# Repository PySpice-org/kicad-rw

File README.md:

# KiCad-RW : Python library to read/write KiCad Sexpr file format

[![KiCadRW
license](https://img.shields.io/pypi/l/KiCadRW.svg)](https://pypi.python.org/pypi/KiCadRW)
[![KiCadRW python
version](https://img.shields.io/pypi/pyversions/KiCadRW.svg)](https://pypi.python.org/pypi/KiCadRW)

[![KiCadRW last
version](https://img.shields.io/pypi/v/KiCadRW.svg)](https://pypi.python.org/pypi/KiCadRW)

**Quick Links**

  - [Devel Branch](https://github.com/FabriceSalvaire/kicad-rw/tree/devel)
  - [Production Branch](https://github.com/FabriceSalvaire/kicad-rw/tree/master)

## Overview

### What is KiCaD-RW ?

**A WORK IN PROGRESS...**

**keywords:** kicad, 6, sexpr, python, schema

**KiCad-RW** is a Python module to read the KiCad version 6 schema file format
(<span class="title-ref">.kicad\_sch</span> file extension) and to compute the netlist which is not
actually stored by KiCad. This module is standalone and independent of the KiCad Python API, thus it
don't require KiCad to work.

**Examples of use cases:**

  - perform checks on circuit
  - export a BOM
  - generate a customised SPICE netlist, see [PySpice](https://github.com/FabriceSalvaire/PySpice)
  - generate a [LaTeX/Tikz](https://ctan.org/pkg/pgf?lang=en) graphic **TO BE IMPLEMENTED**
  - generate a draft for [Circuit\_macros](https://ece.uwaterloo.ca/~aplevich/Circuit_macros), a
    tool for drawing electric high quality circuits, see
    <span class="title-ref">CircuitMacrosDumper</span>
  - etc.

**KiCad-RW** uses the Python library [sexpdata](https://github.com/jd-boyd/sexpdata) to parse the
file.

**How to go further:**

  - KiCad uses Sexpr format, thus we don't have so many tools and a DTD like for XML
  - We must use an external library to parse Sexpr format: sexpdata actually
  - We must be able to parse the file without the need of KiCad, especially if we think KiCad is a
    reference EDA software
  - We must not write tons of code to handle this format...
  - We must try to auto-learn the KiCad format from a reference file collection and generate an OO
    API (fully automatic, jinja template)

[Look at this project](https://github.com/FabriceSalvaire/kicad-rw/projects/1)

[Comprehensive bibliography and relevant links on the
topic](https://github.com/FabriceSalvaire/kicad-rw/blob/main/LINKS.md)

### Where is the Documentation ?

*TO BE COMPLETED*

### Where to get help or talk about KiCaD-RW ?

*TO BE COMPLETED*:

### What are the main features ?

### How to install it ?

*TO BE COMPLETED*

## Pull Request Recommendation

To make it easier to merge your pull request, you should divide your PR into smaller and
easier-to-verify units.

Please do not make a pull requests with a lot of modifications which are difficult to check.

## Credits

Authors: [Fabrice Salvaire](http://fabrice-salvaire.fr) and
[contributors](https://github.com/FabriceSalvaire/kicad-rw/blob/master/CONTRIBUTORS.md)

## News

### V0 2020-05-xx

Started project...

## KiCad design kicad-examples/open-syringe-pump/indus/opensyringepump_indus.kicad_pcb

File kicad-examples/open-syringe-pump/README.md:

# OpenSyringePump Project

Example of a four-layer CMS board designed with KiCad by the [Electrolab](https://www.electrolab.fr)
team (Mehdi Khairy) during the Covid-19 pandemy to make an open hardware syringe pump, the
[OpenSyringePump](https://www.opensyringepump.com/en/design-bom/electronic-parts) project.

All documents are hosted on this Git repository
https://code.electrolab.fr/covid-19/opensyringepump/-/tree/master/hardware/indus/opensyringe_indus

## Hardware License

The **OpenSyringePump** project led by the **ELECTROLAB** non profit organization, and all documents
produced through the development process are under Creative Commons license:
https://creativecommons.org/licenses/by-sa/4.0

See for more details https://www.opensyringepump.com/en/project-license

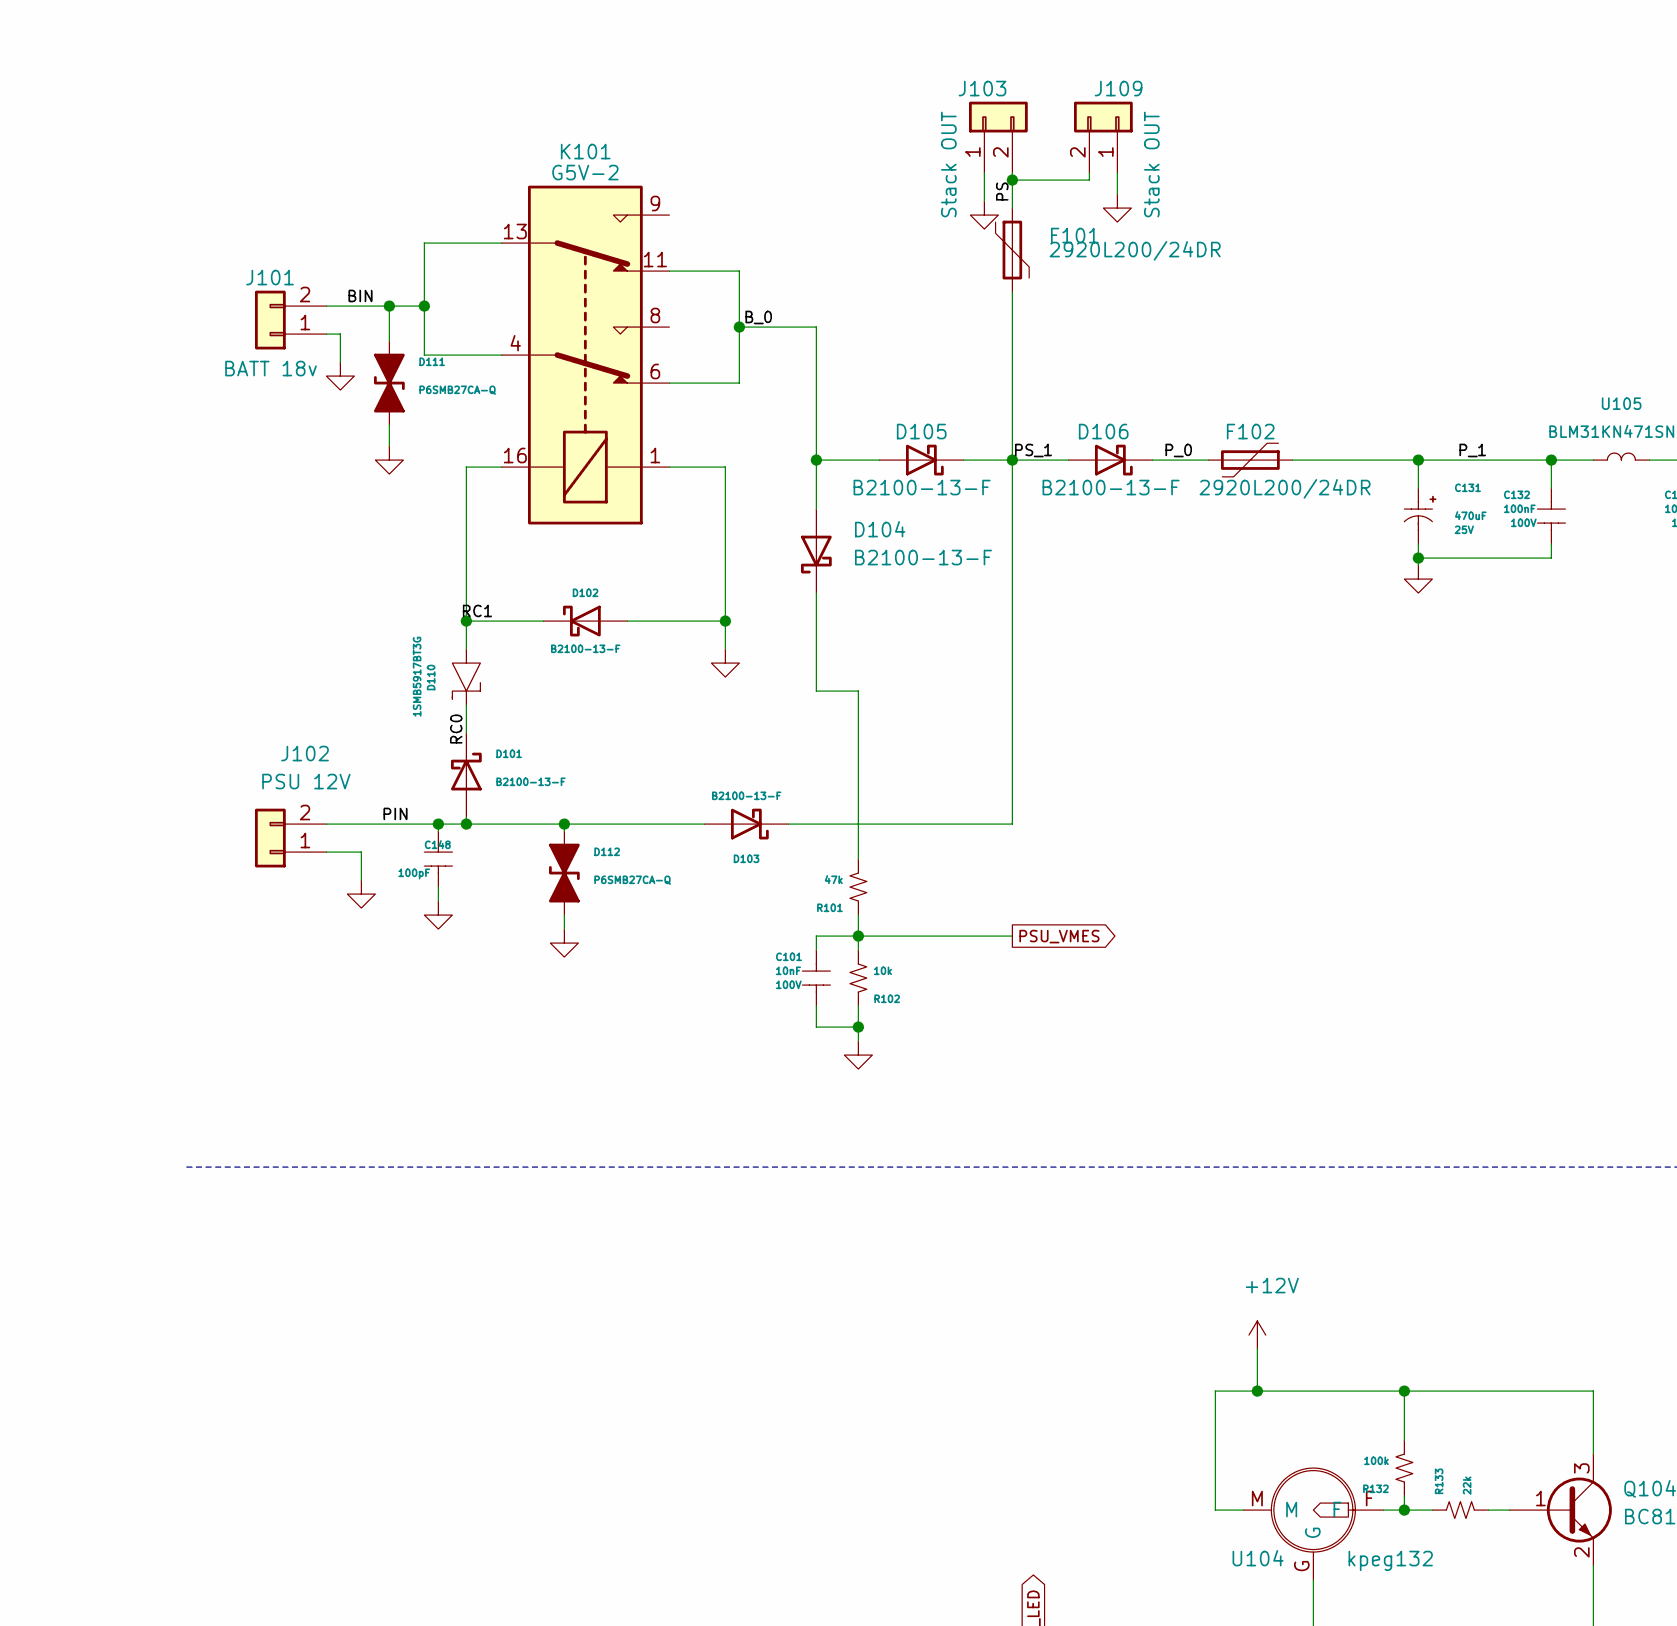
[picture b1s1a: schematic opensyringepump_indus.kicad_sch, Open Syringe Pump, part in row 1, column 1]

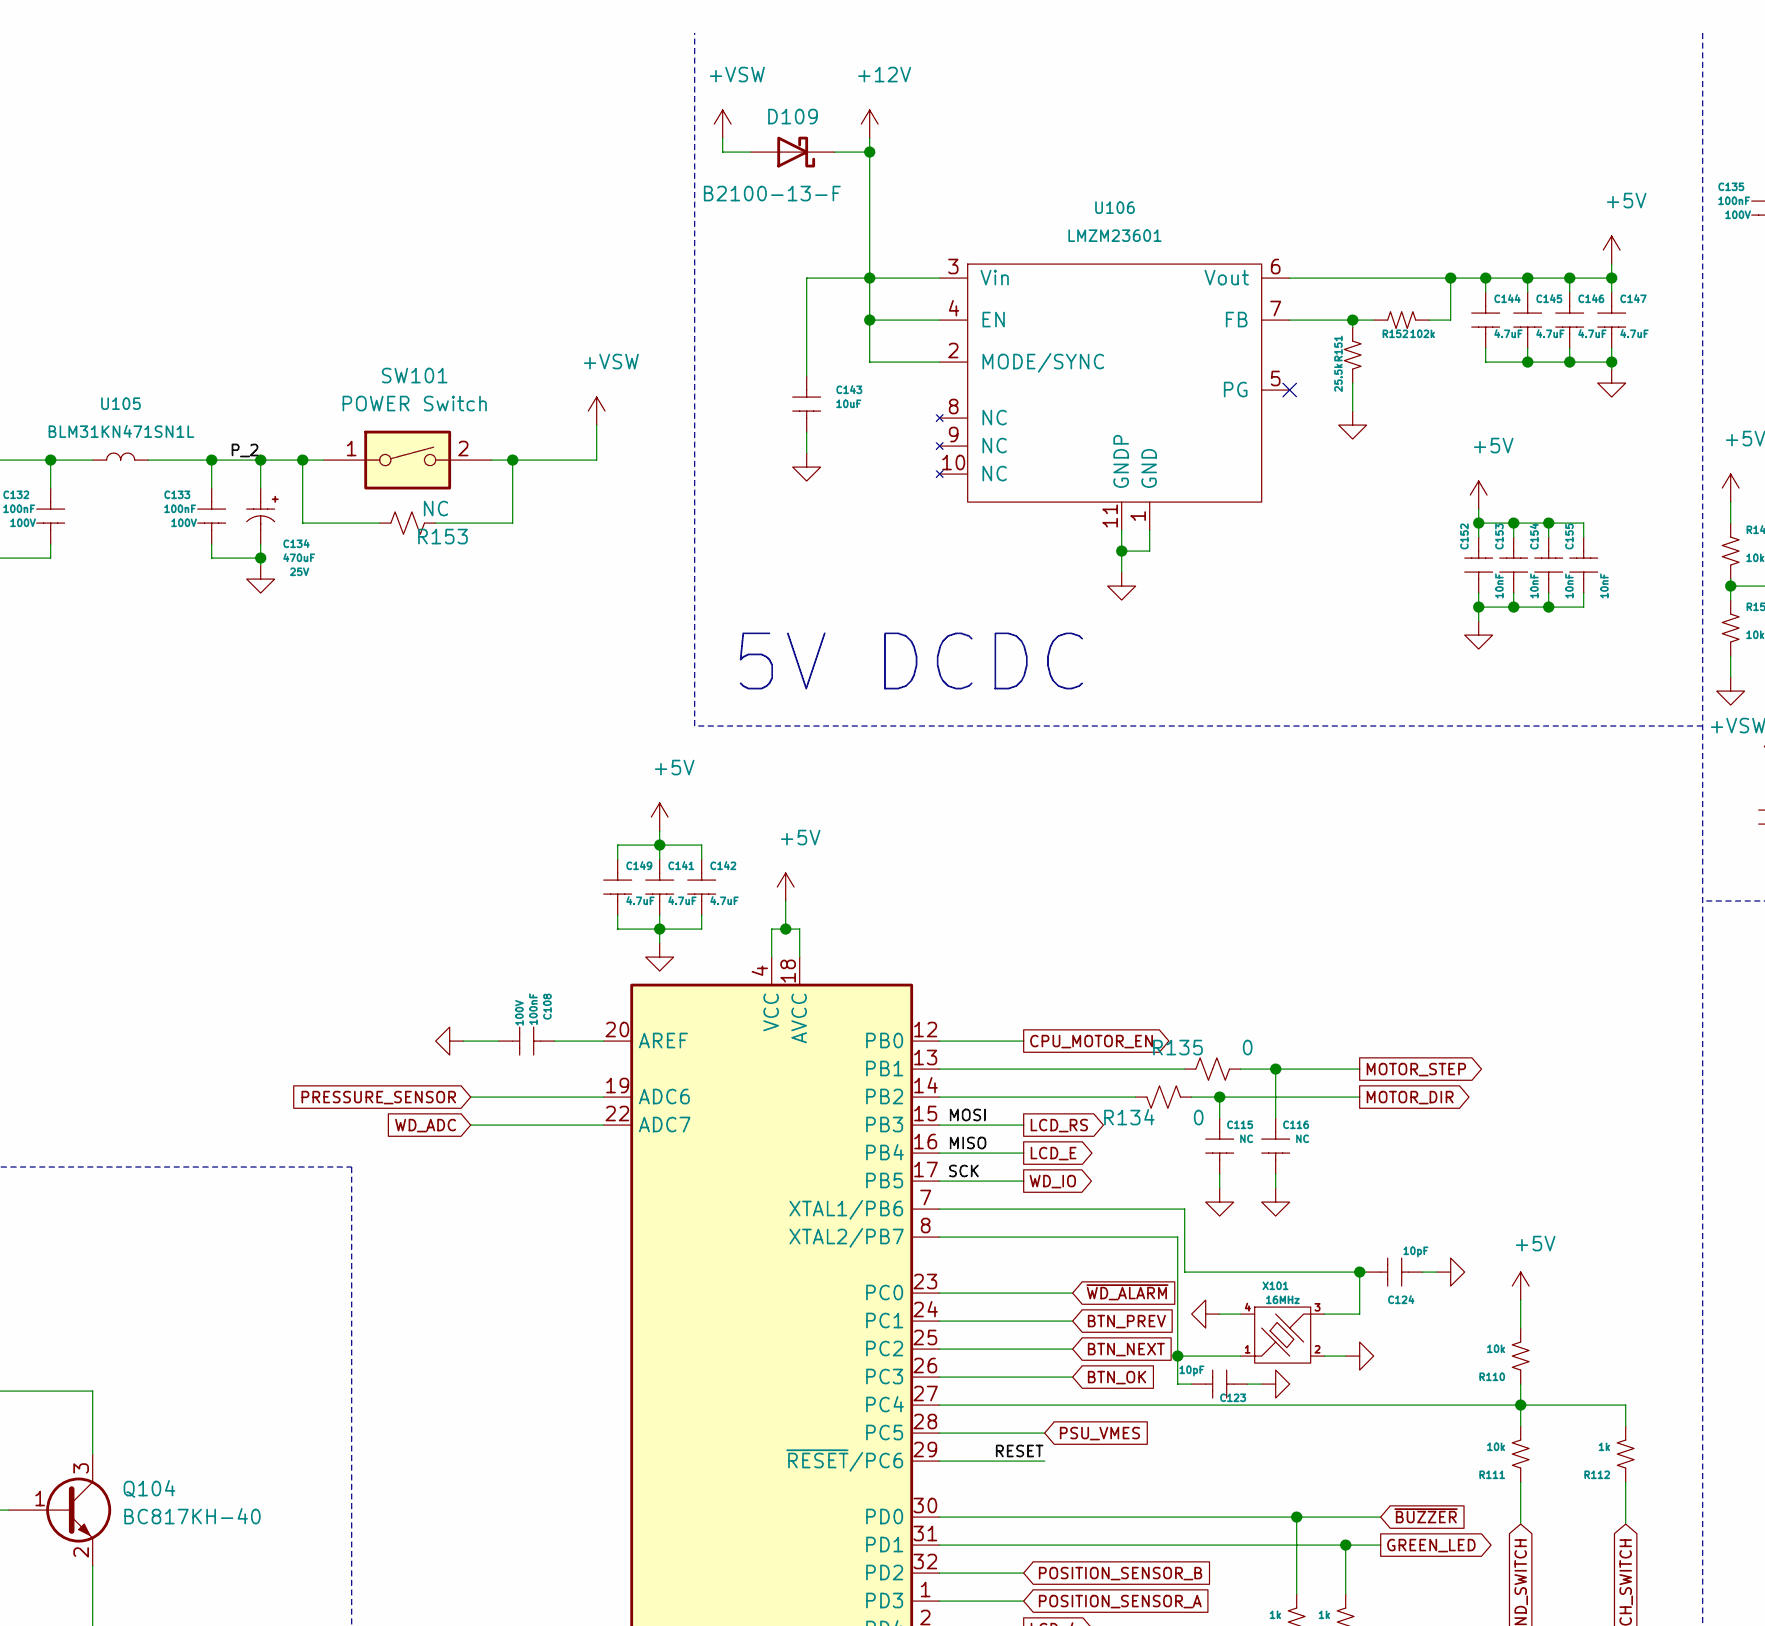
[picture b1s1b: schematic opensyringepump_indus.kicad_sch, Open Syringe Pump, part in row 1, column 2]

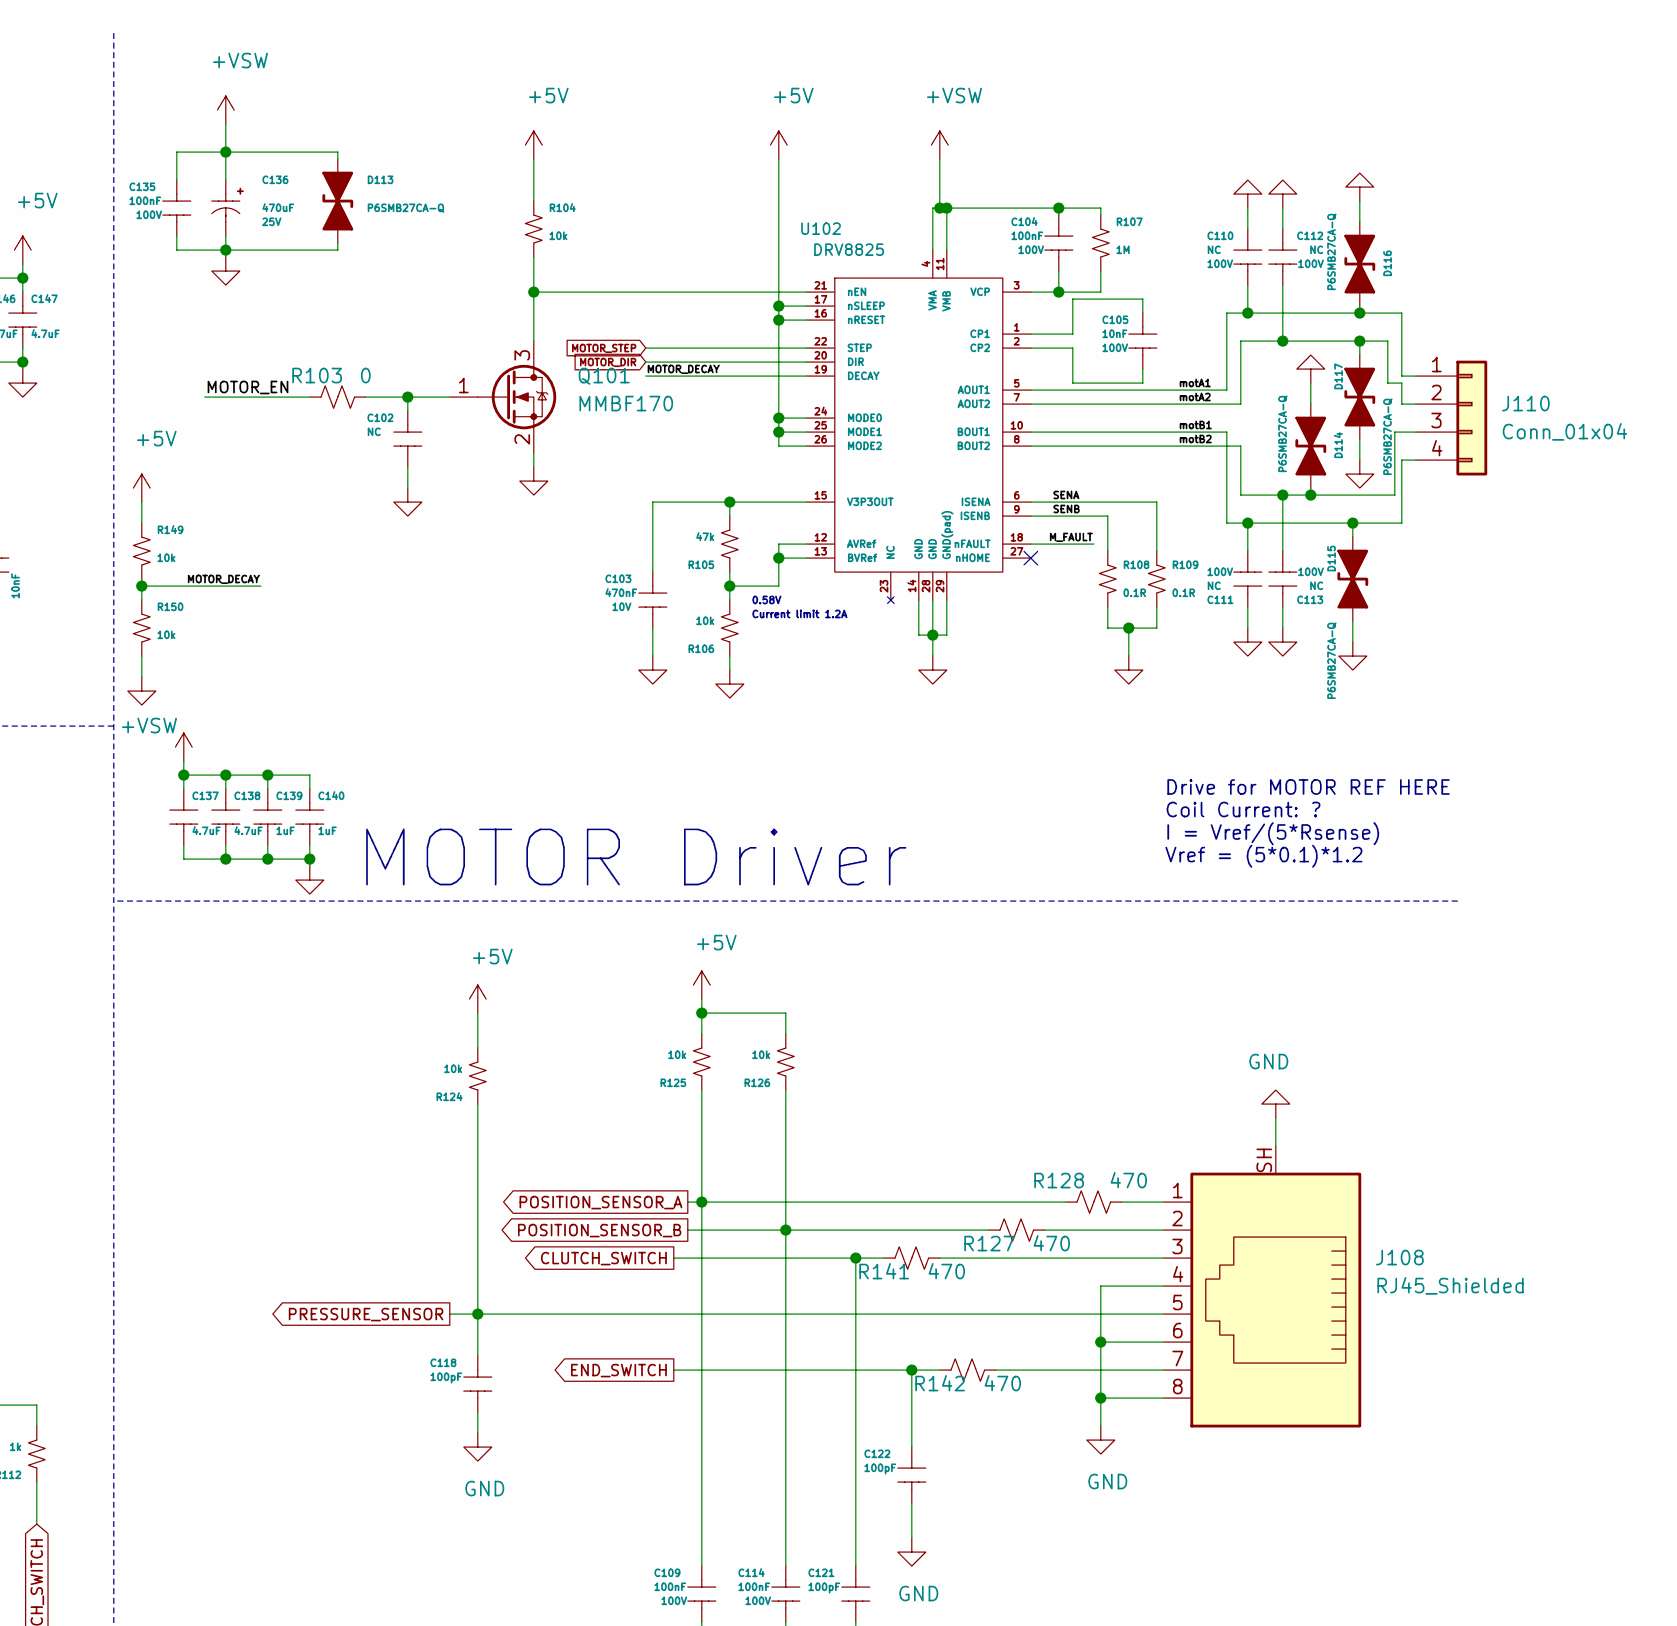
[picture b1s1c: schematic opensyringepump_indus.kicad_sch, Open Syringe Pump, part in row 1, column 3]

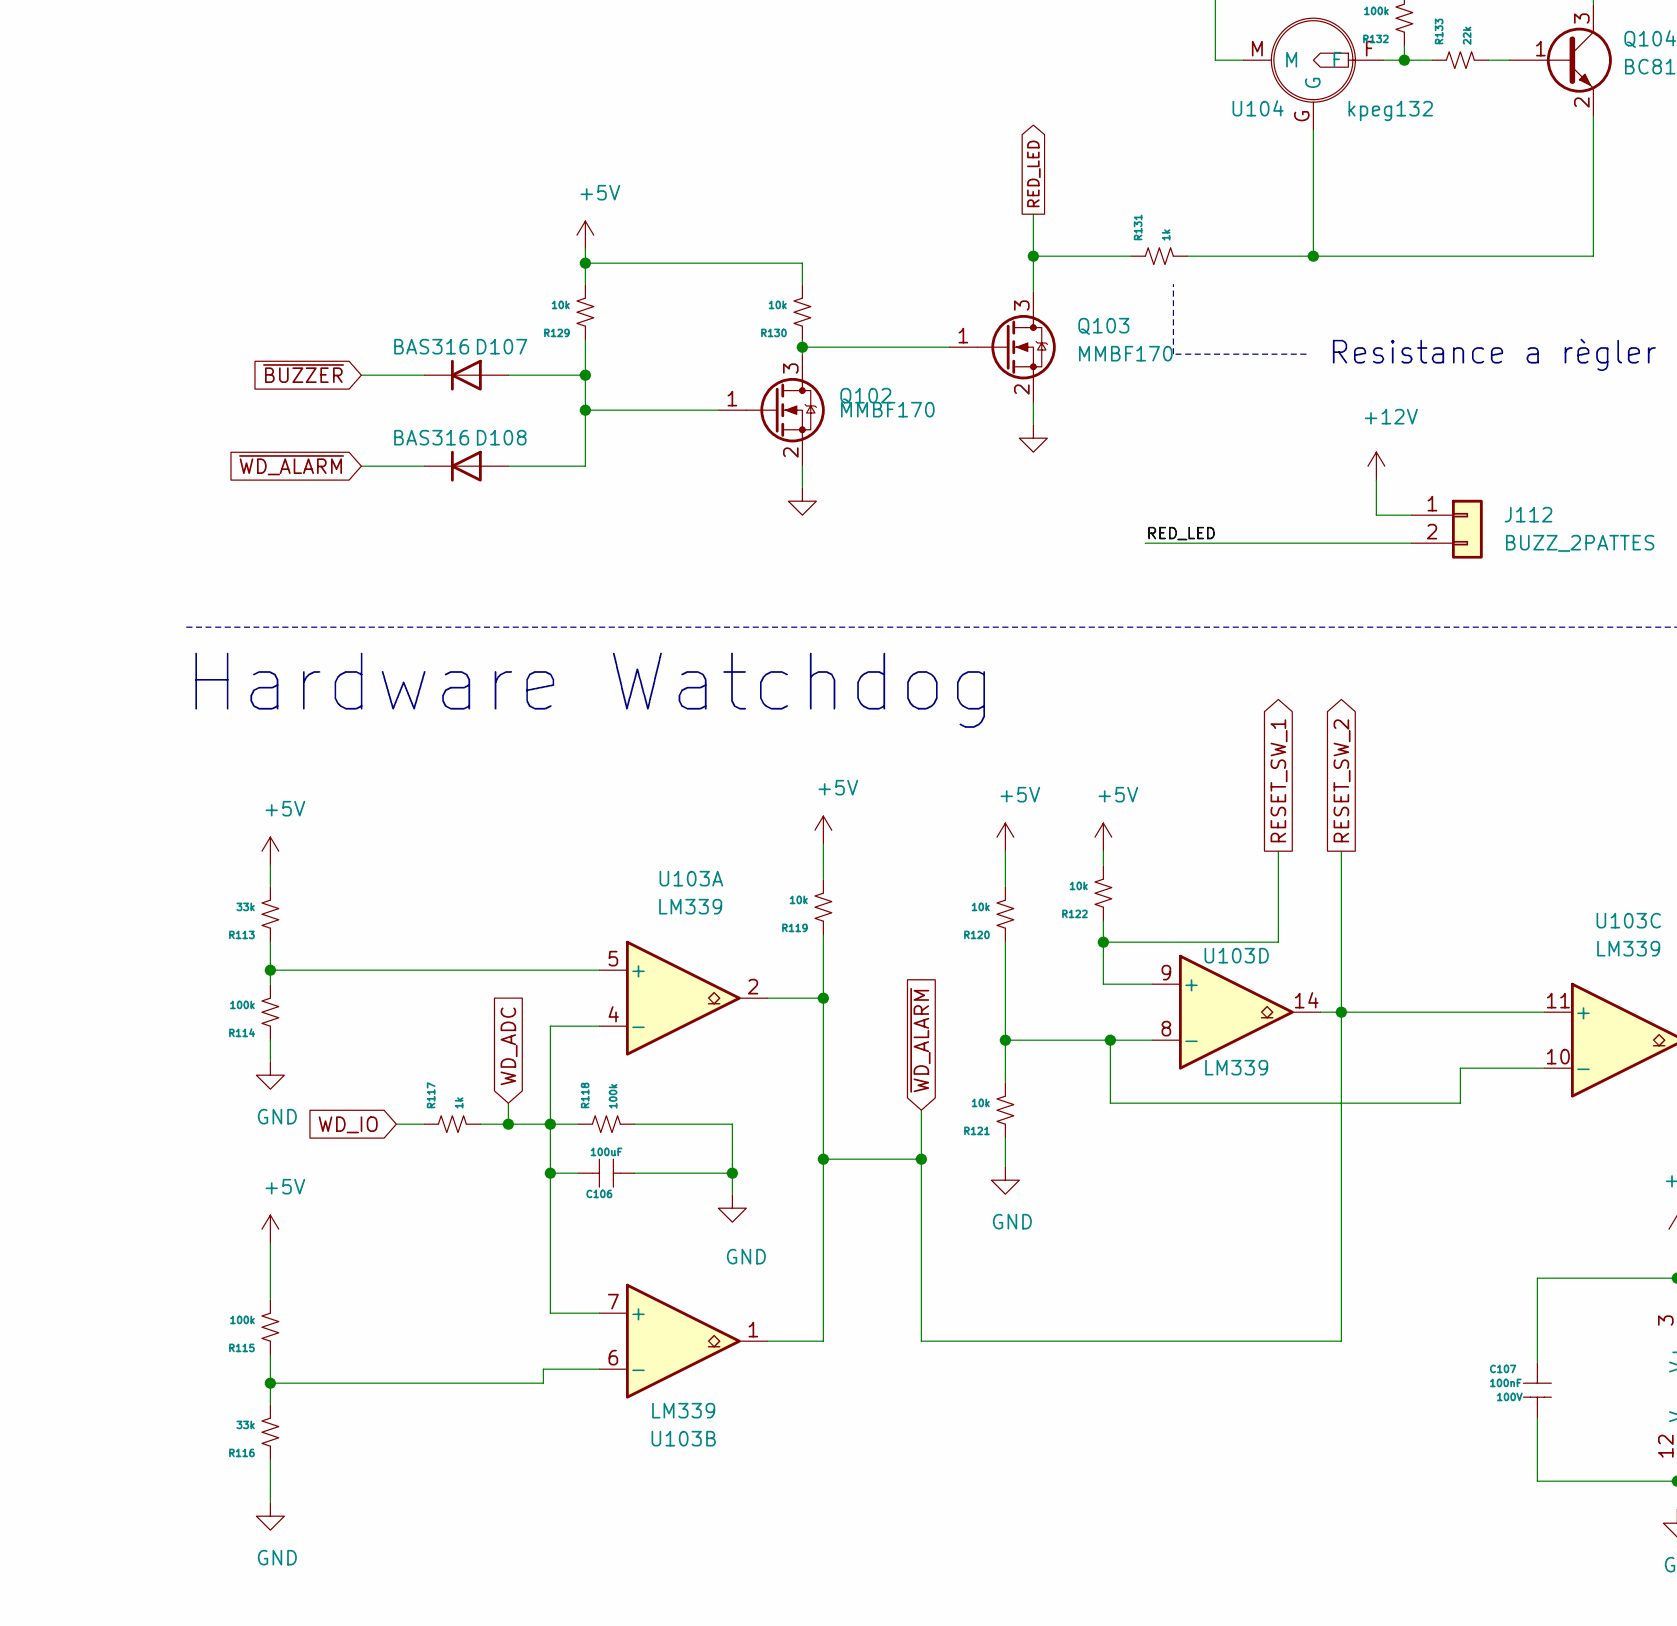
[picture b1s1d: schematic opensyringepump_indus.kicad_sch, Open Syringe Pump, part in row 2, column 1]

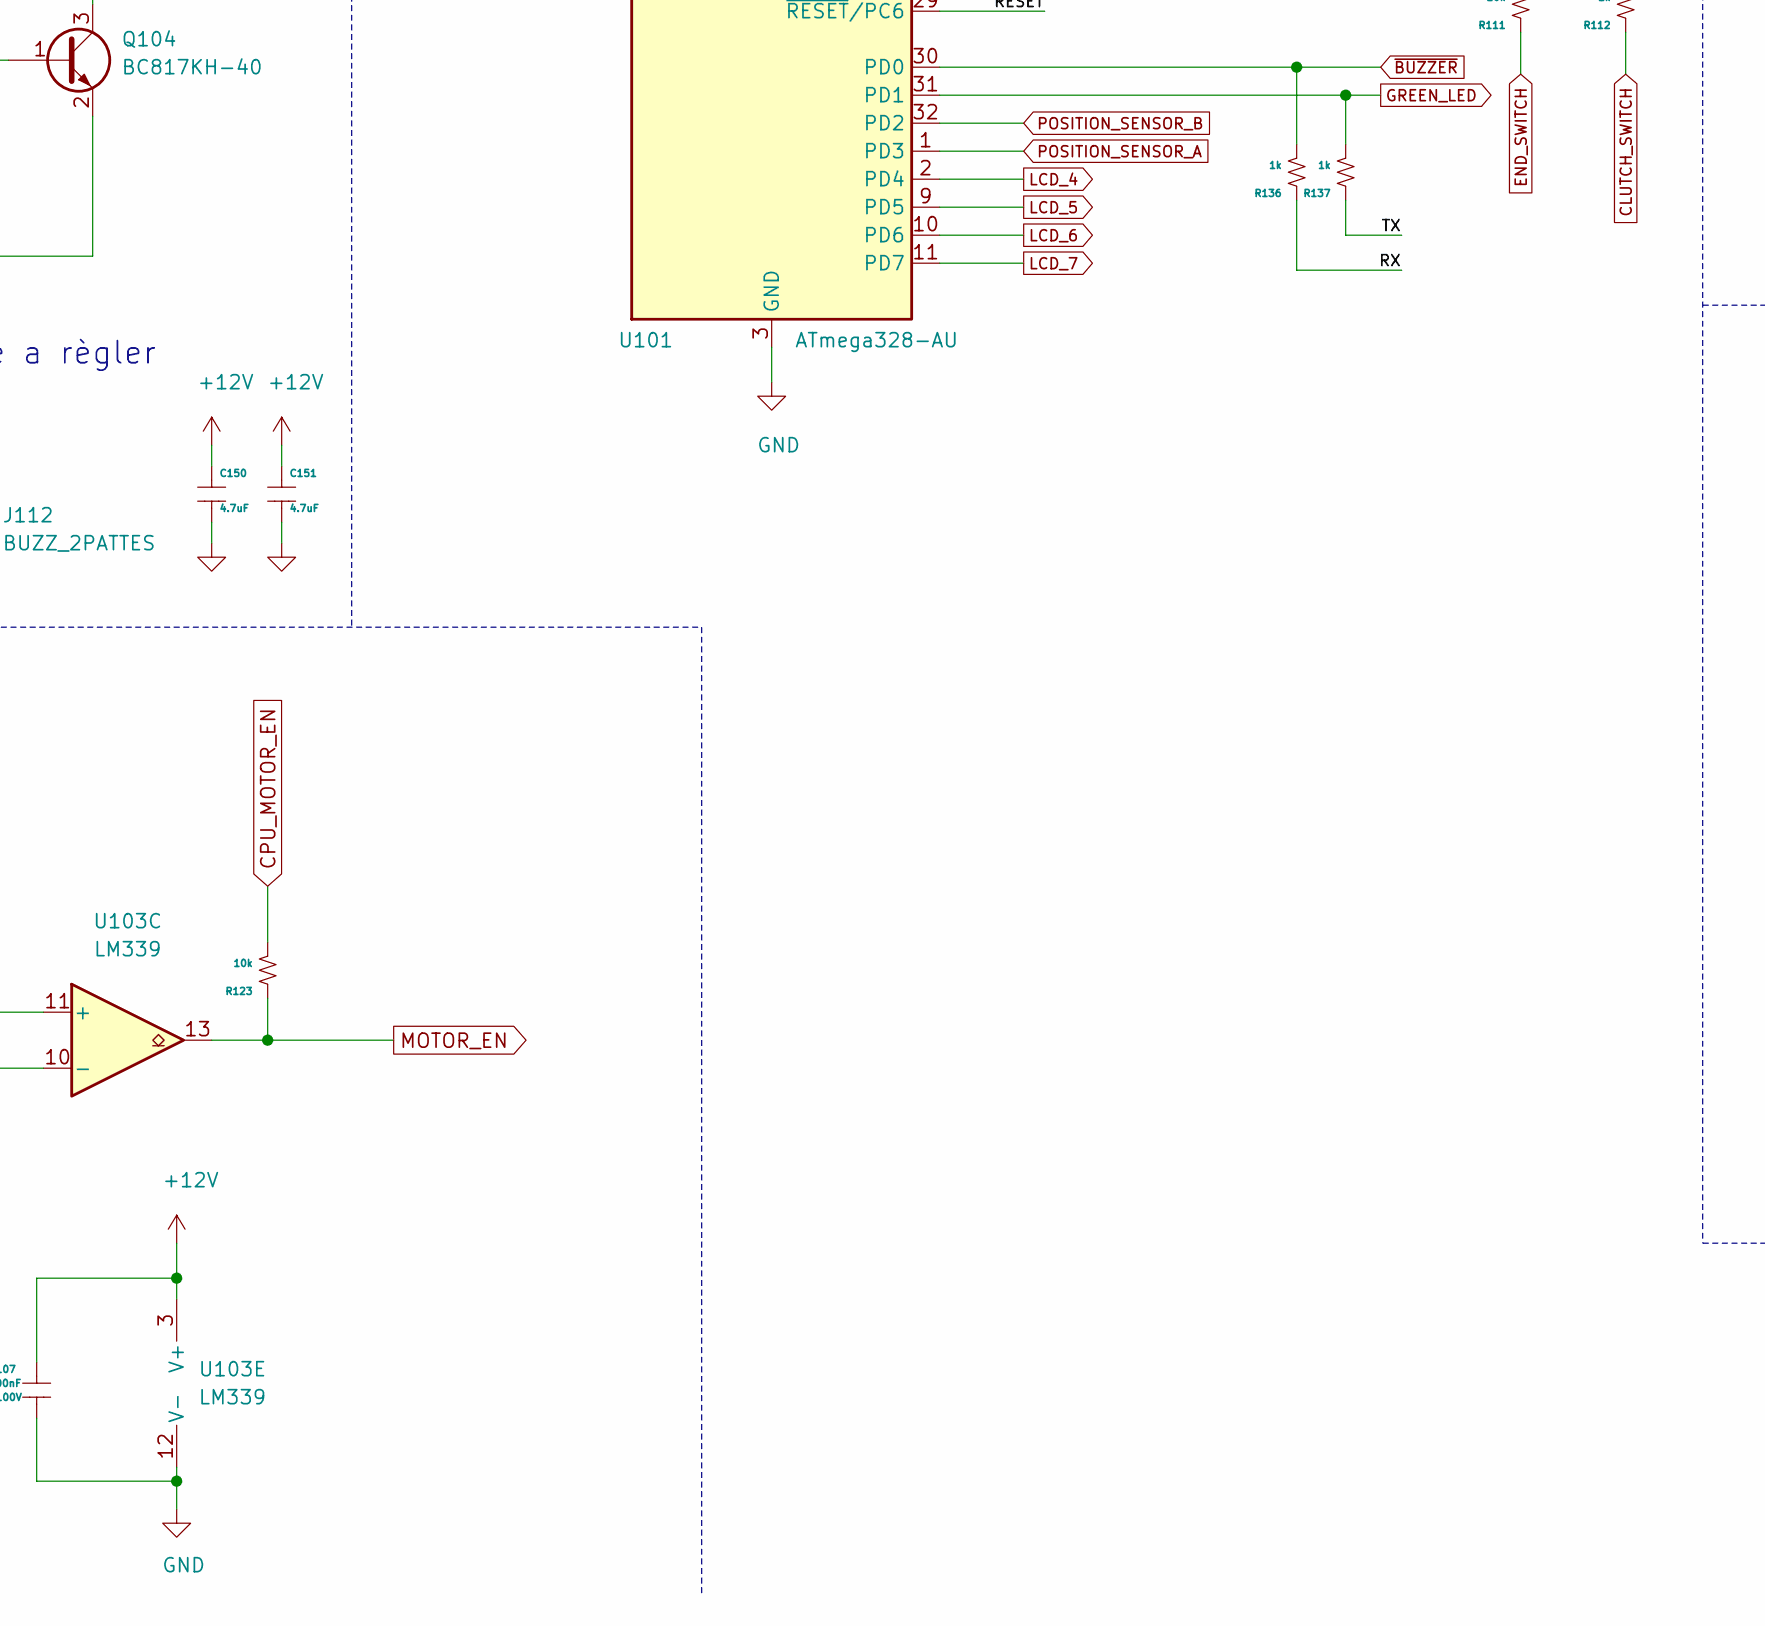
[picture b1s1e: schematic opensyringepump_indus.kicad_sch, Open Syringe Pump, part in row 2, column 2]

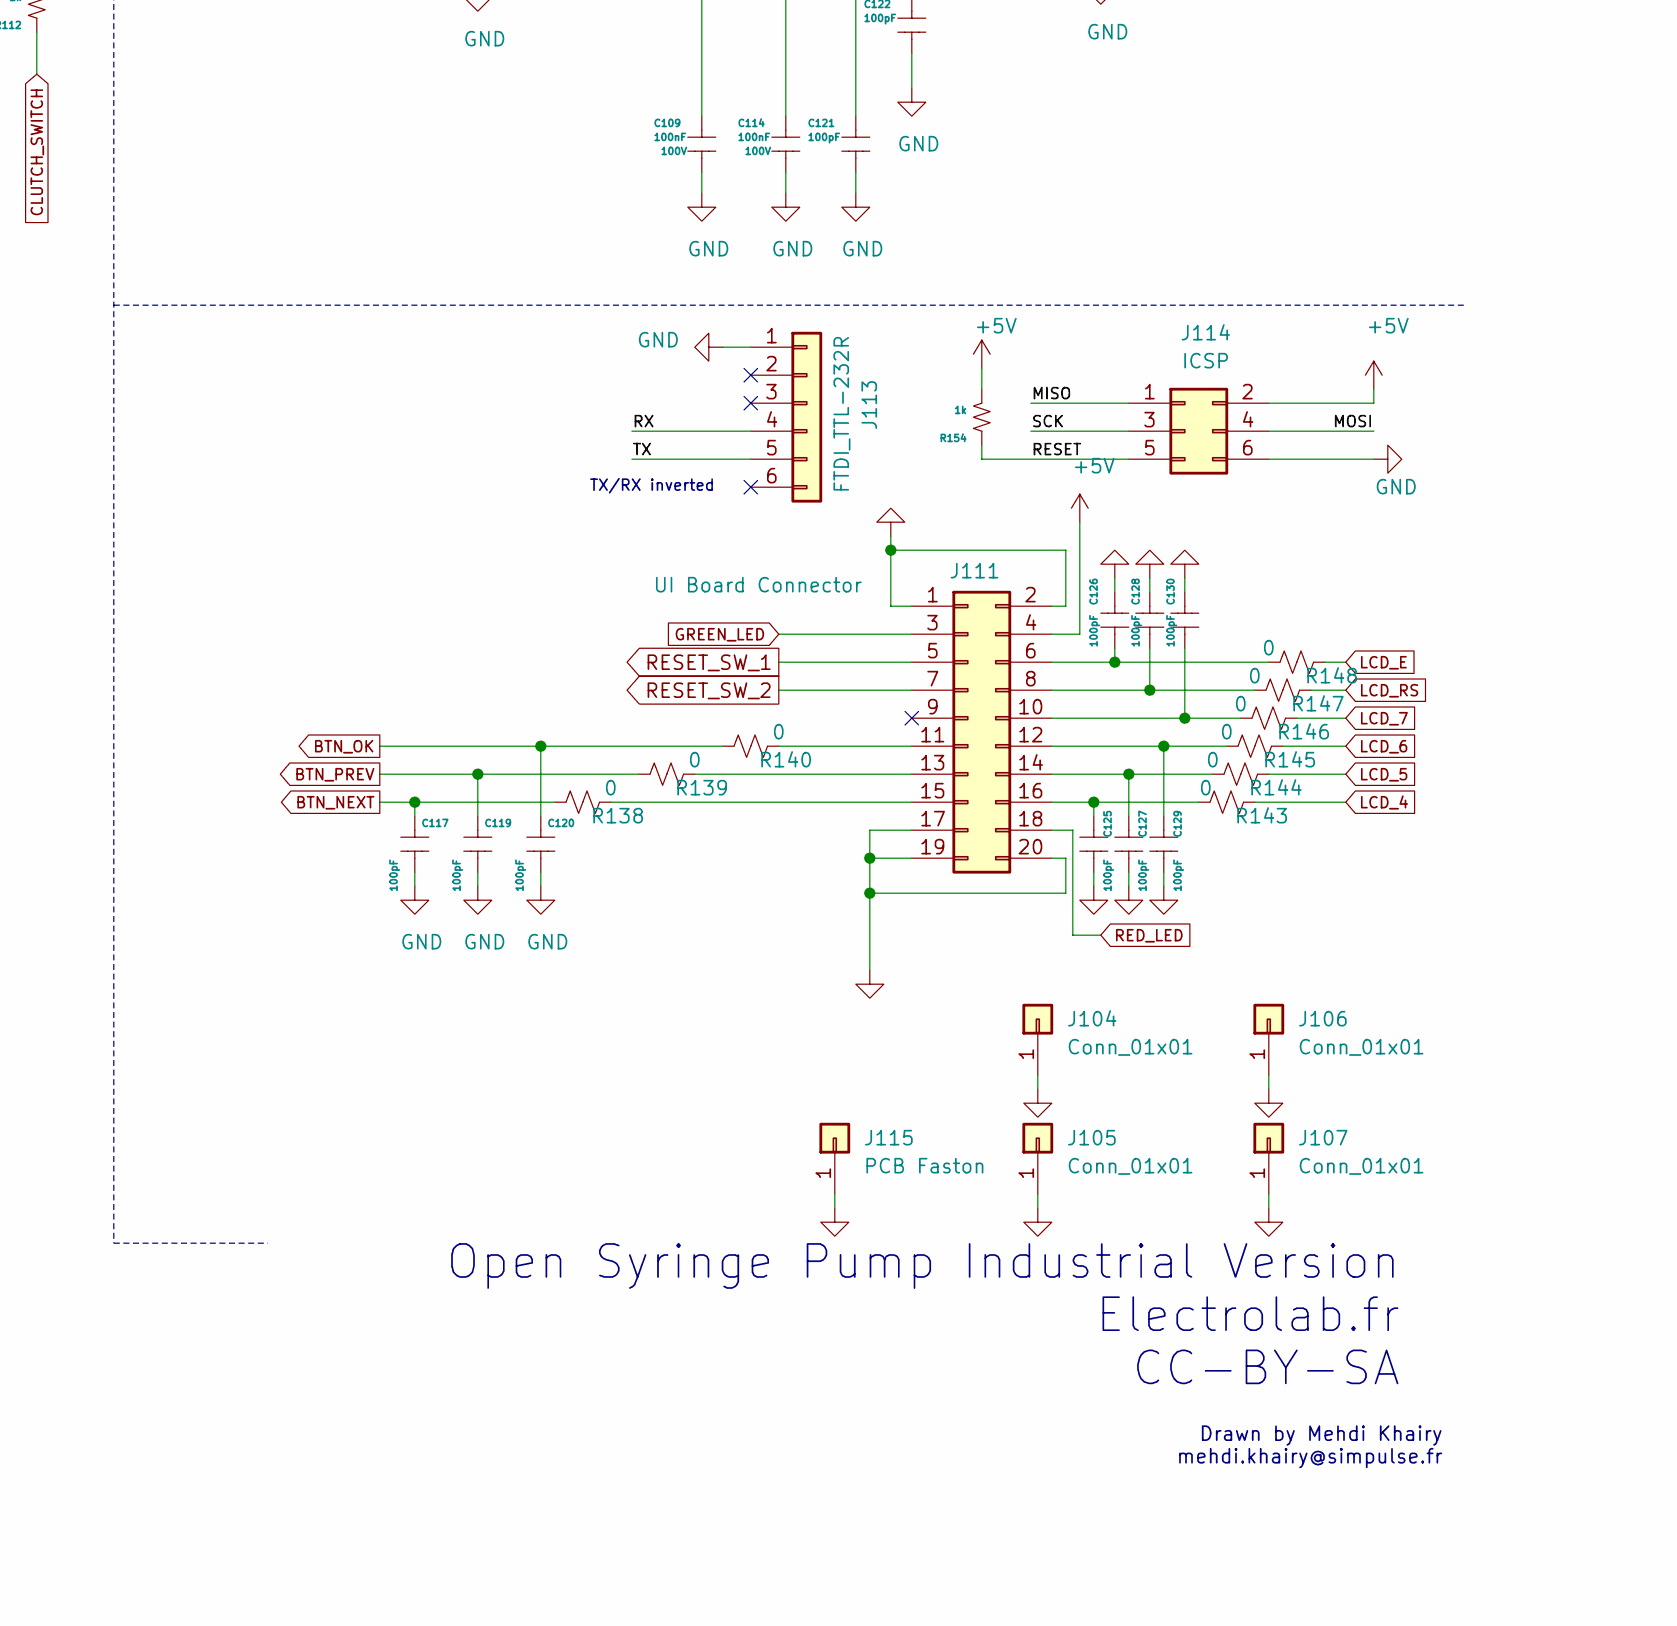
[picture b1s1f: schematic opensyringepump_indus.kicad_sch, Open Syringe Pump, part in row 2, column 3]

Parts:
C101, C105, C152, C153, C154, C155: 10nF; SM0603
C102, C110, C111, C112, C113, C115, C116: NC; SM0603
C103: 470nF; SM0603
C104, C107, C108, C109, C114, C132, C133, C135: 100nF; SM0603
C106: 100uF; SM1210
C117, C118, C119, C120, C121, C122, C125, C126, C127, C128, C129, C130, C148: 100pF; SM0603
C123, C124: 10pF; SM0603
C131, C134, C136: 470uF; SMD_ECAP_G_R10
C137, C138, C141, C142, C144, C145, C146, C147, C149, C150, C151: 4.7uF; SM0805
C139, C140: 1uF; SM0805
C143: 10uF; SM1210
D101, D102, D103, D104, D105, D106, D109: B2100-13-F; D_SMB
D107, D108: BAS316; D_SOD-323
D110: 1SMB5917BT3G; D_SMB
D111, D112, D113, D114, D115, D116, D117: P6SMB27CA-Q; D_SMB
F101, F102: 2920L200/24DR; 2920L
J101: BATT 18v; Molex_KK-254_AE-6410-02A_1x02_P2.54mm_Vertical
J102: PSU 12V; Molex_KK-254_AE-6410-02A_1x02_P2.54mm_Vertical
J103, J109: Stack OUT; Molex_KK-254_AE-6410-02A_1x02_P2.54mm_Vertical
J104, J105, J106, J107: Conn_01x01; MountingHole_4.5mm_Pad
J108: RJ45_Shielded; 95552-2887
J110: Conn_01x04; Molex_KK-254_AE-6410-04A_1x04_P2.54mm_Vertical
J111: UI Board Connector; PinHeader_2x10_P2.54mm_Vertical
J112: BUZZ_2PATTES; PinHeader_1x02_P2.54mm_Vertical
J113: FTDI_TTL-232R; PinHeader_1x06_P2.54mm_Vertical
J114: ICSP; PinHeader_2x03_P2.54mm_Vertical
J115: PCB Faston; 0-0726388-2
K101: G5V-2; Relay_DPDT_Omron_G5V-2
Q101, Q102, Q103: MMBF170; SOT-23
Q104: BC817KH-40; SOT-23
R101, R105: 47k; SM0603
R102, R104, R106, R110, R111, R119, R120, R121, R122, R123, R124, R125, R126, R129, R130, R149, R150: 10k; SM0603
R103, R134, R135, R138, R139, R140, R143, R144, R145, R146, R147, R148: 0; SM0603
R107: 1M; SM0603
R108, R109: 0.1R; SM1206
R112, R117, R131, R136, R137, R154: 1k; SM0603
R113, R116: 33k; SM0603
R114, R115, R118, R132: 100k; SM0603
R127, R128, R141, R142: 470; SM0603
R133: 22k; SM0603
R151: 25.5k; SM0603
R152: 102k; SM0603
R153: NC; SM0603
SW101: POWER Switch; Molex_KK-254_AE-6410-02A_1x02_P2.54mm_Vertical
U101: ATmega328-AU; TQFP-32_7x7mm_P0.8mm
U102: DRV8825; HTSSOP28_PowerPad
U103: LM339; SOIC-14_3.9x8.7mm_P1.27mm
U104: kpeg132
U105: BLM31KN471SN1L; SM1206
U106: LMZM23601; QFN-0x5_EP_3.8x3_Pitch0.6mm
X101: 16MHz; xtal_3.2x2.5

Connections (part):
+5V: C141.1, C142.1, C144.1, C145.1, C146.1, C147.1, C149.1, C152.2, C153.2, C154.2, C155.2, J111.4, J114.2, R104.1, R110.2, R113.2, R115.2, R119.2, R120.2, R122.2, R124.2, R125.2, R126.2, R129.2, R130.2, R149.1, R152.2, R154.2, U101.4 (VCC), U101.6 (VCC), U101.18 (AVCC), U102.16 (nRESET), U102.17 (nSLEEP), U102.24 (MODE0), U102.25 (MODE1), U102.26 (MODE2), U106.6 (Vout)
+12V: C107.1, C143.1, C150.1, C151.1, D109.1 (K), J112.1, Q104.3 (C), R132.2, U103.3 (V+), U104.M, U106.2 (MODE/SYNC), U106.3 (Vin), U106.4 (EN)
+VSW: C104.1, C135.1, C136.2, C137.1, C138.1, C139.1, C140.1, D109.2 (A), D113.1 (A1), R107.1, R153.1, SW101.2, U102.4 (VMA), U102.11 (VMB)
/BIN: D111.1 (A1), J101.2, K101.4, K101.13
/B_0: D104.2 (A), D105.2 (A), K101.6, K101.11
/MOTOR_DECAY: R149.2, R150.1, U102.19 (DECAY)
/M_FAULT: U102.18 (nFAULT)
/PIN: C148.1, D101.2 (A), D103.2 (A), D112.1 (A1), J102.2
/PS: F101.1, J103.2, J109.2
/PS_1: D103.1 (K), D105.1 (K), D106.2 (A), F101.2
/P_0: D106.1 (K), F102.2
/P_1: C131.2, C132.1, F102.1, U105.1
/P_2: C133.1, C134.2, R153.2, SW101.1, U105.2
/RC0: D101.1 (K), D110.1 (K)
/RC1: D102.1 (K), D110.2 (A), K101.16
/RESET: J114.5, R154.1, U101.29 (~RESET~/PC6)
/RX: J113.4, R136.1
/SENA: R109.1, U102.6 (ISENA)
/SENB: R108.1, U102.9 (ISENB)
/TX: J113.5, R137.1
/motA1: C110.2, D116.1 (A1), J110.1, U102.5 (AOUT1)
/motA2: C112.2, D117.1 (A1), J110.2, U102.7 (AOUT2)
/motB1: C111.2, D115.1 (A1), J110.4, U102.10 (BOUT1)
/motB2: C113.2, D114.1 (A1), J110.3, U102.8 (BOUT2)
BTN_NEXT: C117.1, R138.2, U101.25 (PC2)
BTN_OK: C120.1, R140.2, U101.26 (PC3)
BTN_PREV: C119.1, R139.2, U101.24 (PC1)
CLUTCH_SWITCH: C121.1, R112.1, R141.2
CPU_MOTOR_EN: R123.2, U101.12 (PB0)
END_SWITCH: C122.1, R111.1, R142.2
GND: C101.2, C102.2, C103.2, C106.2, C107.2, C108.2, C109.2, C110.1, C111.1, C112.1, C113.1, C114.2, C115.2, C116.2, C117.2, C118.2, C119.2, C120.2, C121.2, C122.2, C123.1, C124.1, C125.2, C126.2, C127.2, C128.2, C129.2, C130.2, C131.1, C132.2, C133.2, C134.1, C135.2, C136.1, C137.2, C138.2, C139.2, C140.2, C141.2, C142.2, C143.2, C144.2, C145.2, C146.2, C147.2, C148.2, C149.2, C150.2, C151.2, C152.1, C153.1, C154.1, C155.1, D102.2 (A), D111.2 (A2), D112.2 (A2), D113.2 (A2), D114.2 (A2), D115.2 (A2), D116.2 (A2), D117.2 (A2), J101.1, J102.1, J103.1, J104.1, J105.1, J106.1, J107.1, J108.4, J108.6, J108.8, J108.SH, J109.1, J111.1, J111.2, J111.17, J111.19, J111.20, J113.1, J114.6, J115.1, K101.1, Q101.2 (S), Q102.2 (S)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
GREEN_LED: J111.3, R137.2, U101.31 (PD1)
LCD_4: R143.1, U101.2 (PD4)
LCD_5: R144.1, U101.9 (PD5)
LCD_6: R145.1, U101.10 (PD6)
LCD_7: R146.1, U101.11 (PD7)
LCD_E: J114.1, R148.1, U101.16 (PB4)
LCD_RS: J114.4, R147.1, U101.15 (PB3)
MOTOR_DIR: C115.1, R134.1, U102.20 (DIR)
MOTOR_EN: R103.2, R123.1, U103.13
MOTOR_STEP: C116.1, R135.1, U102.22 (STEP)
unnamed: C102.1, Q101.1 (G), R103.1
unnamed: C103.1, R105.2, U102.15 (V3P3OUT)
unnamed: C104.2, R107.2, U102.3 (VCP)
unnamed: C105.1, U102.1 (CP1)
unnamed: C105.2, U102.2 (CP2)
unnamed: C108.1, U101.20 (AREF)
unnamed: C123.2, U101.8 (XTAL2/PB7), X101.1
unnamed: C124.2, U101.7 (XTAL1/PB6), X101.3
unnamed: C125.1, J111.16, R143.2
unnamed: C126.1, J111.6, R148.2
unnamed: C127.1, J111.14, R144.2
unnamed: C128.1, J111.8, R147.2
unnamed: C129.1, J111.12, R145.2
unnamed: C130.1, J111.10, R146.2
unnamed: D104.1 (K), R101.2
unnamed: D107.2 (A), D108.2 (A), Q102.1 (G), R129.1
unnamed: J108.1, R128.1
unnamed: J108.2, R127.1
unnamed: J108.3, R141.1
unnamed: J108.7, R142.1
unnamed: J111.11, R140.1
unnamed: J111.13, R139.1
unnamed: J111.15, R138.1
unnamed: Q101.3 (D), R104.2, U102.21 (nEN)
unnamed: Q102.3 (D), Q103.1 (G), R130.1
unnamed: Q104.1 (B), R133.2
unnamed: Q104.2 (E), R131.2, U104.G
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
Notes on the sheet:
Hardware Watchdog
Resistance a règler
5V DCDC
TX/RX inverted
0.58V
Current limit 1.2A
MOTOR Driver
Drive for MOTOR REF HERE Coil Current: ? I = Vref/(5*Rsense) Vref = (5*0.1)*1.2
Open Syringe Pump Industrial Version Electrolab.fr CC-BY-SA
Drawn by Mehdi Khairy mehdi.khairy@simpulse.fr

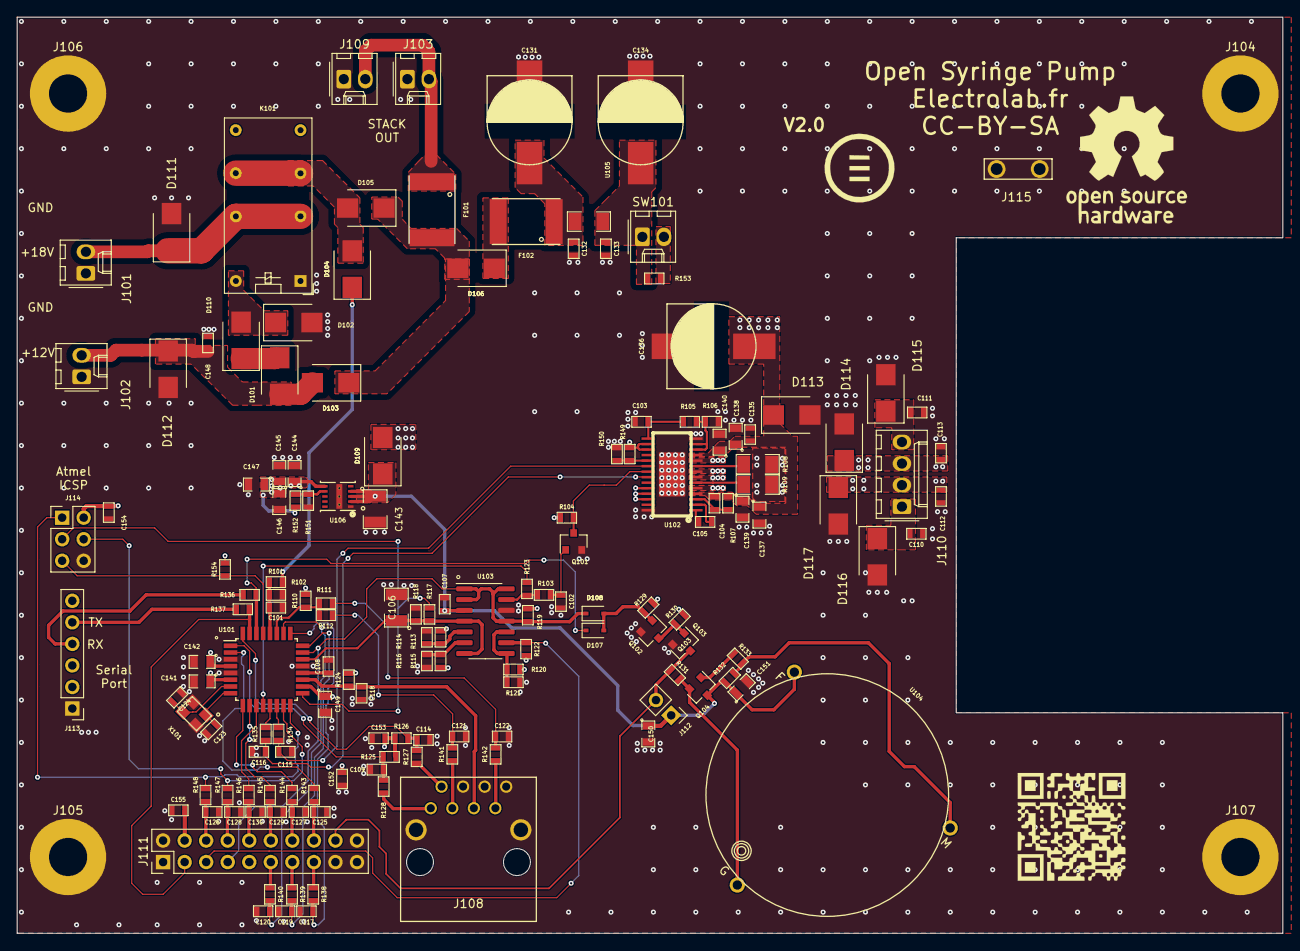
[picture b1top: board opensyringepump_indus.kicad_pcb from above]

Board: 4 copper layers, 149.2 x 108.0 mm, 156 parts (0 on the bottom side), 86 nets.

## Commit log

2021-05-12 KiCadTools
2021-05-12 KiCadTools: cleanup
2021-05-13 add label, cleanup
2021-05-13 KiCadTools: add examples
2021-05-13 KiCadTools/.gitignore
2021-05-13 KiCadTools: complete
2021-05-13 KiCadTools: improve
2021-05-13 KiCadTools: remove pin angle
2021-05-13 KiCadTools: movre code
2021-05-13 KiCadTools: match wire
2021-05-13 KiCadTools: add getter
2021-05-13 KiCadTools: comment
2021-05-13 KiCadTools: test netlist builder
2021-05-13 KiCadTools: fix
2021-05-13 add KiCad
2021-05-13 KiCadTools: improve API
2021-05-13 KiCadTools: improve dump
2021-05-13 KiCadTools: readme, add CircuitMacrosDumper
2021-05-13 KiCadTools: readme
2021-05-16 -> KiCadRW
2021-05-16 gitignore
2021-05-16 add license
2021-05-16 add setup
2021-05-16 github
2021-05-16 readme
2021-05-16 add tasks
2021-05-16 gitattributes
2021-05-16 setup
2021-05-16 gh-pages
2021-05-16 use pelican for readme
2021-05-16 kicad-example -> +s
2021-05-16 add capacitive-half-wave-rectification-pre-zener kicad files
2021-05-16 fixes code after git filter
2021-05-16 gitignores
2021-05-16 add rewrite test
2021-05-16 -> AGPL
2021-05-16 implement logging
2021-05-16 implement objectifier
2021-05-16 implement xpath
2021-05-16 fix objectifier for relative path
2021-05-16 -> deprecated
2021-05-16 kicad example: add open-syringe-pump industrial board
2021-05-16 example
2021-05-16 manifest
2021-05-16 task/release
2021-05-16 main init
2021-05-16 setup fix
2022-10-19 -> doc/notes
2022-10-23 capacitive-half-wave-rectification-pre-zener rename
2022-10-23 add electrolab-cta-control-board example
2022-10-23 add symbols
2022-10-23 improve objectifier
2022-10-23 add AVR DA DB generator
2022-10-23 add sexp version od avr_da_db generator
2022-10-23 rename
2022-10-23 cleanup and lower case modules
2022-10-23 fix for sexpdata upgrade
2022-10-23 add sexp module
2022-10-23 refactor
2022-10-23 gitgnore
2022-10-23 add symbol module
2022-10-23 cleanup
2022-10-23 csv -> data
